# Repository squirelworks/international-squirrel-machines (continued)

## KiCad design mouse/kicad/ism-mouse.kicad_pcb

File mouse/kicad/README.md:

# ISM Mouse — KiCad

Generated by `python3 scripts/build_mouse.py`.

| File | Role |
|------|------|
| `ism-mouse.kicad_sch` / `.kicad_pcb` / `.kicad_pro` | Project |
| `sym-lib-table` / `fp-lib-table` | Project-local tables (`${KIPRJMOD}/../../common/kicad`, `${KICAD8_*}`) |
| `erc.rpt` / `drc.rpt` | Last `--severity-error` reports (expect 0 errors) |

Shared symbols / optical-sensor footprint: `common/kicad/`.

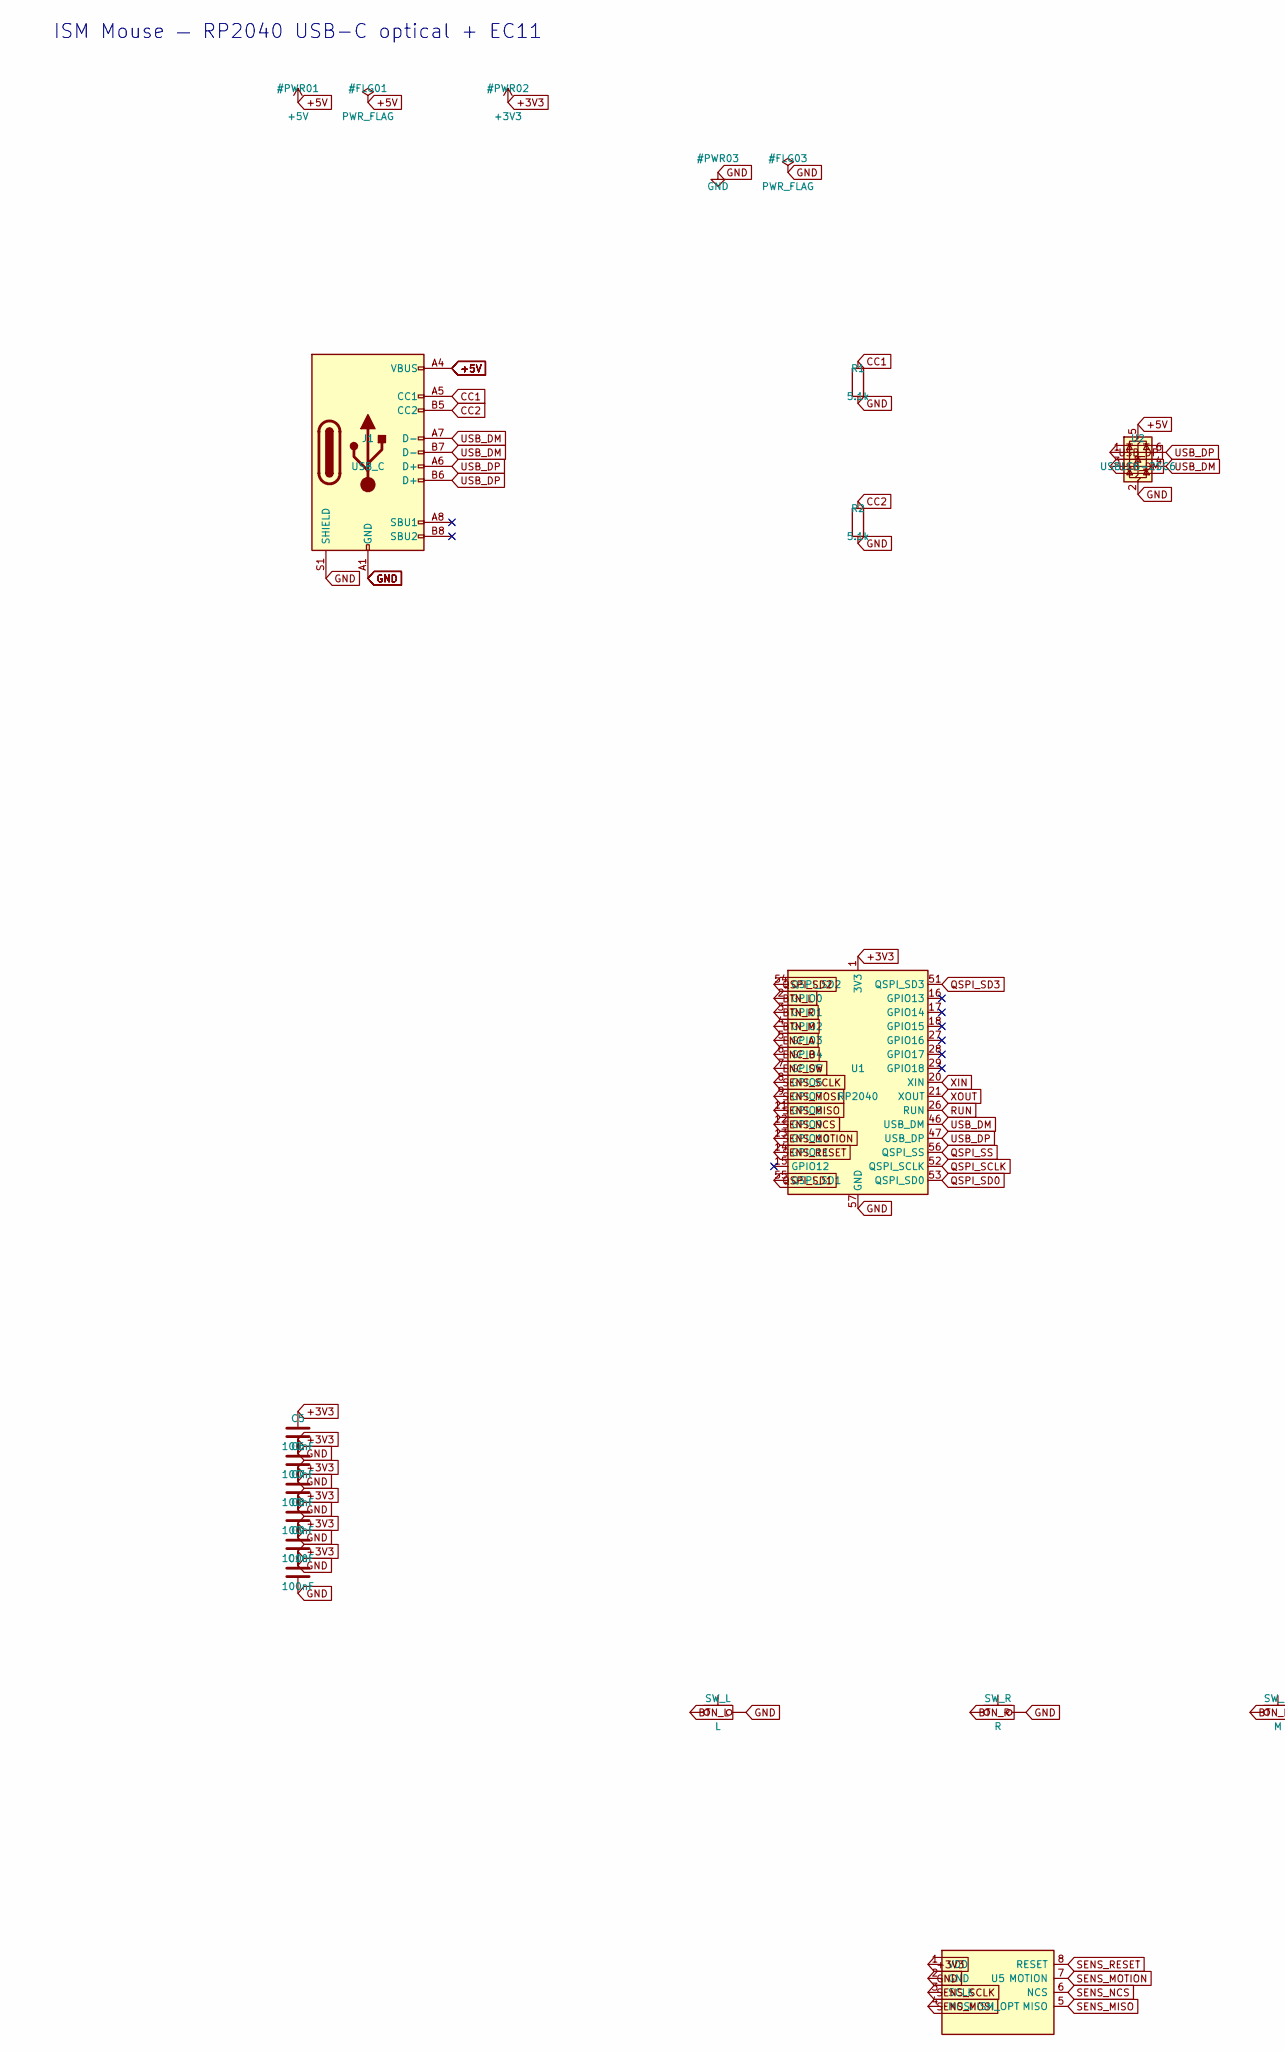
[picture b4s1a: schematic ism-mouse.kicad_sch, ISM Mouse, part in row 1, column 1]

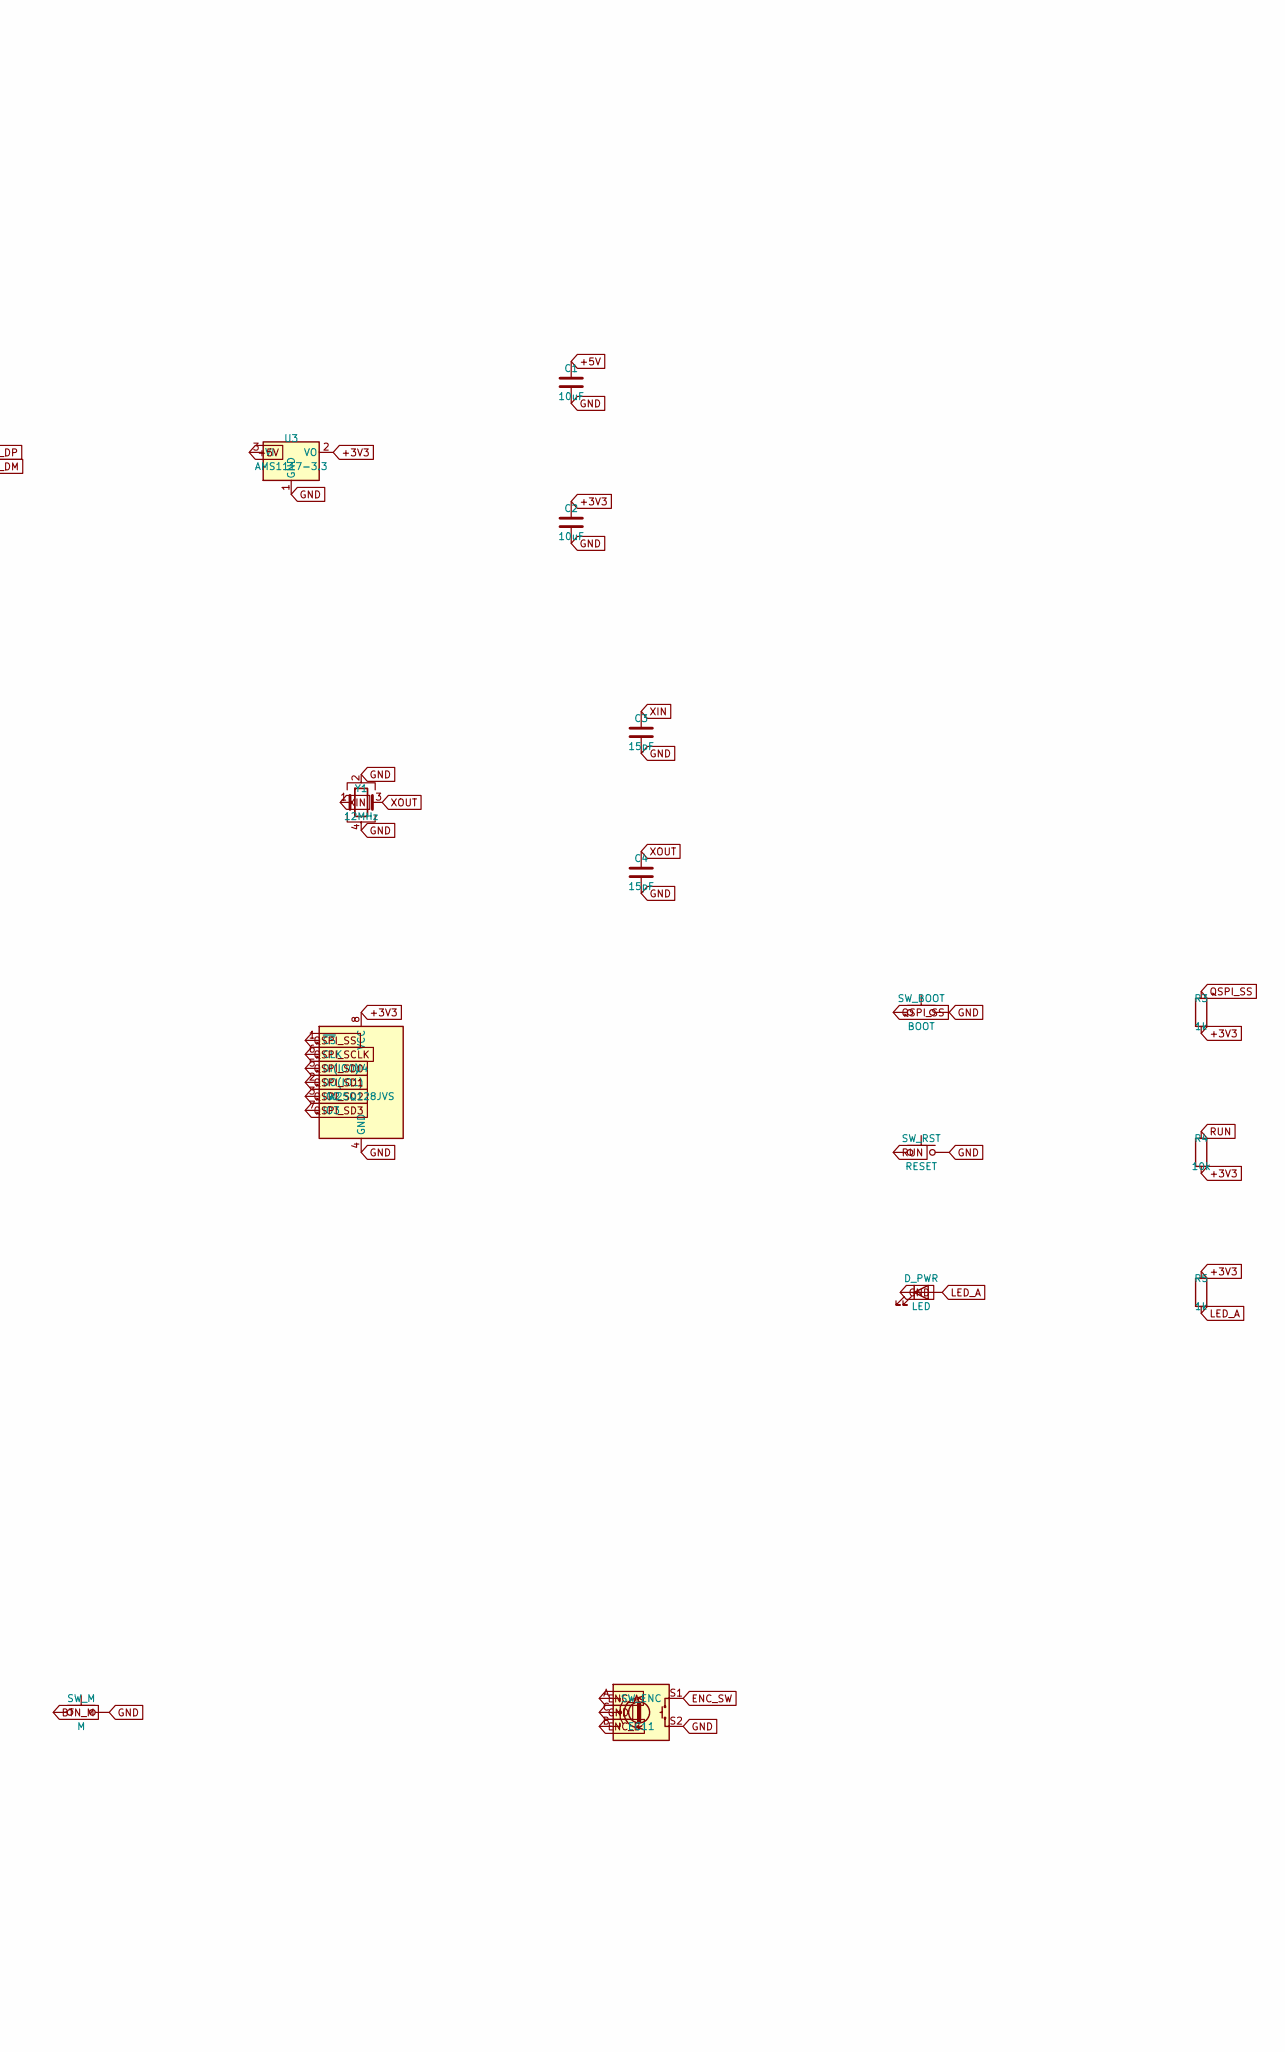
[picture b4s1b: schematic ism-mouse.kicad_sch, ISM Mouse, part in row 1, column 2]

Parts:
C1, C2: 10uF; C_0805_2012Metric; LCSC C15850
C3, C4: 15pF; C_0603_1608Metric; LCSC C1007
C5, C6, C7, C8, C9, C10: 100nF; C_0603_1608Metric; LCSC C14663
D_PWR: LED; LED_0603_1608Metric; LCSC C2286
J1: USB_C; USB_C_Receptacle_GCT_USB4105-xx-A_16P_TopMnt_Horizontal; MPN USB4105-GF-A; LCSC C165948
R1, R2: 5.1k; R_0603_1608Metric; LCSC C23244
R3, R5: 1k; R_0603_1608Metric; LCSC C21190
R4: 10k; R_0603_1608Metric; LCSC C25804
SW_BOOT: BOOT; SW_SPST_PTS645; LCSC C318884
SW_ENC: EC11; RotaryEncoder_Alps_EC11E-Switch_Vertical_H20mm; MPN EC11E; LCSC C318975
SW_L: L; SW_SPST_PTS645; LCSC C318884
SW_M: M; SW_SPST_PTS645; LCSC C318884
SW_R: R; SW_SPST_PTS645; LCSC C318884
SW_RST: RESET; SW_SPST_PTS645; LCSC C318884
U1: RP2040; QFN-56-1EP_7x7mm_P0.4mm_EP3.2x3.2mm; MPN RP2040; LCSC C2040
U2: USBLC6-2SC6; SOT-23-6; LCSC C7519
U3: AMS1117-3.3; TO-252-3_TabPin2; LCSC C6187
U4: W25Q128JVS; SOIC-8_3.9x4.9mm_P1.27mm; LCSC C97521
U5: ISM_OPT; ISM_OpticalSensor_8pad; MPN ISM-OPT-1
Y1: 12MHz; Crystal_SMD_3225-4Pin_3.2x2.5mm; LCSC C13713

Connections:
+3V3: C2.1, C5.1, C6.1, C7.1, C8.1, C9.1, C10.1, R3.2, R4.2, R5.1, U1.1 (3V3), U1.10, U1.22, U1.23, U1.33, U1.42, U1.43, U1.44, U1.45, U1.48, U1.49, U1.50, U3.2 (VO), U4.8 (VCC), U5.1 (VDD)
+5V: C1.1, J1.A4 (VBUS), J1.A9 (VBUS), J1.B4 (VBUS), J1.B9 (VBUS), U2.5 (VBUS), U3.3 (VI)
BTN_L: SW_L.1, U1.2 (GPIO0)
BTN_M: SW_M.1, U1.4 (GPIO2)
BTN_R: SW_R.1, U1.3 (GPIO1)
CC1: J1.A5 (CC1), R1.1
CC2: J1.B5 (CC2), R2.1
ENC_A: SW_ENC.A, U1.5 (GPIO3)
ENC_B: SW_ENC.B, U1.6 (GPIO4)
ENC_SW: SW_ENC.S1, U1.7 (GPIO5)
GND: C1.2, C2.2, C3.2, C4.2, C5.2, C6.2, C7.2, C8.2, C9.2, C10.2, D_PWR.1 (K), J1.A1 (GND), J1.A8 (SBU1), J1.A12 (GND), J1.B1 (GND), J1.B8 (SBU2), J1.B12 (GND), J1.S1 (SHIELD), R1.2, R2.2, SW_BOOT.2, SW_ENC.C, SW_ENC.S2, SW_L.2, SW_M.2, SW_R.2, SW_RST.2, U1.19, U1.57 (GND), U2.2 (GND), U3.1 (GND), U4.4 (GND), U5.2 (GND), Y1.2, Y1.4; also elsewhere on the board
LED_A: D_PWR.2 (A), R5.2
QSPI_SCLK: U1.52 (QSPI_SCLK), U4.6 (CLK)
QSPI_SD0: U1.53 (QSPI_SD0), U4.5 (DI(IO0))
QSPI_SD1: U1.55 (QSPI_SD1), U4.2 (DO(IO1))
QSPI_SD2: U1.54 (QSPI_SD2), U4.3 (IO2)
QSPI_SD3: U1.51 (QSPI_SD3), U4.7 (IO3)
QSPI_SS: R3.1, SW_BOOT.1, U1.56 (QSPI_SS), U4.1 (~CS)
RUN: R4.1, SW_RST.1, U1.26 (RUN)
SENS_MISO: U1.11 (GPIO8), U5.5 (MISO)
SENS_MOSI: U1.9 (GPIO7), U5.4 (MOSI)
SENS_MOTION: U1.13 (GPIO10), U5.7 (MOTION)
SENS_NCS: U1.12 (GPIO9), U5.6 (NCS)
SENS_RESET: U1.14 (GPIO11), U5.8 (RESET)
SENS_SCLK: U1.8 (GPIO6), U5.3 (SCLK)
USB_DM: J1.A7 (D-), J1.B7 (D-), U1.46 (USB_DM), U2.3 (I/O2), U2.4 (I/O2)
USB_DP: J1.A6 (D+), J1.B6 (D+), U1.47 (USB_DP), U2.1 (I/O1), U2.6 (I/O1)
XIN: C3.1, U1.20 (XIN), Y1.1
XOUT: C4.1, U1.21 (XOUT), Y1.3

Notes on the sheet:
ISM Mouse — RP2040 USB-C optical + EC11

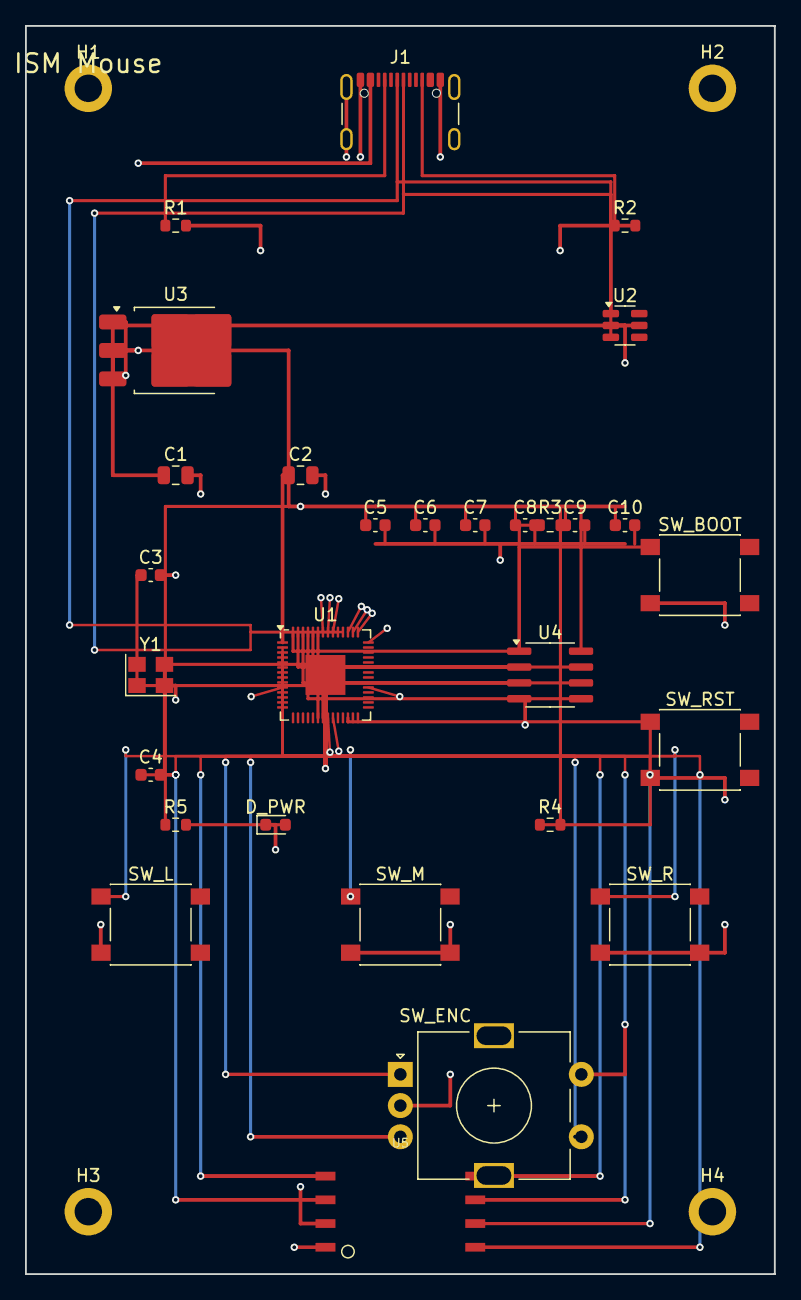
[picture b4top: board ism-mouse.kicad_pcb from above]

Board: 4 copper layers, 60.0 x 100.0 mm, 33 parts (0 on the bottom side), 29 nets.

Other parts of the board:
H1, H2, H3, H4: M2; MountingHole_2.2mm_M2_DIN965_Pad

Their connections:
GND: H1.1, H2.1, H3.1, H4.1; also elsewhere on the board

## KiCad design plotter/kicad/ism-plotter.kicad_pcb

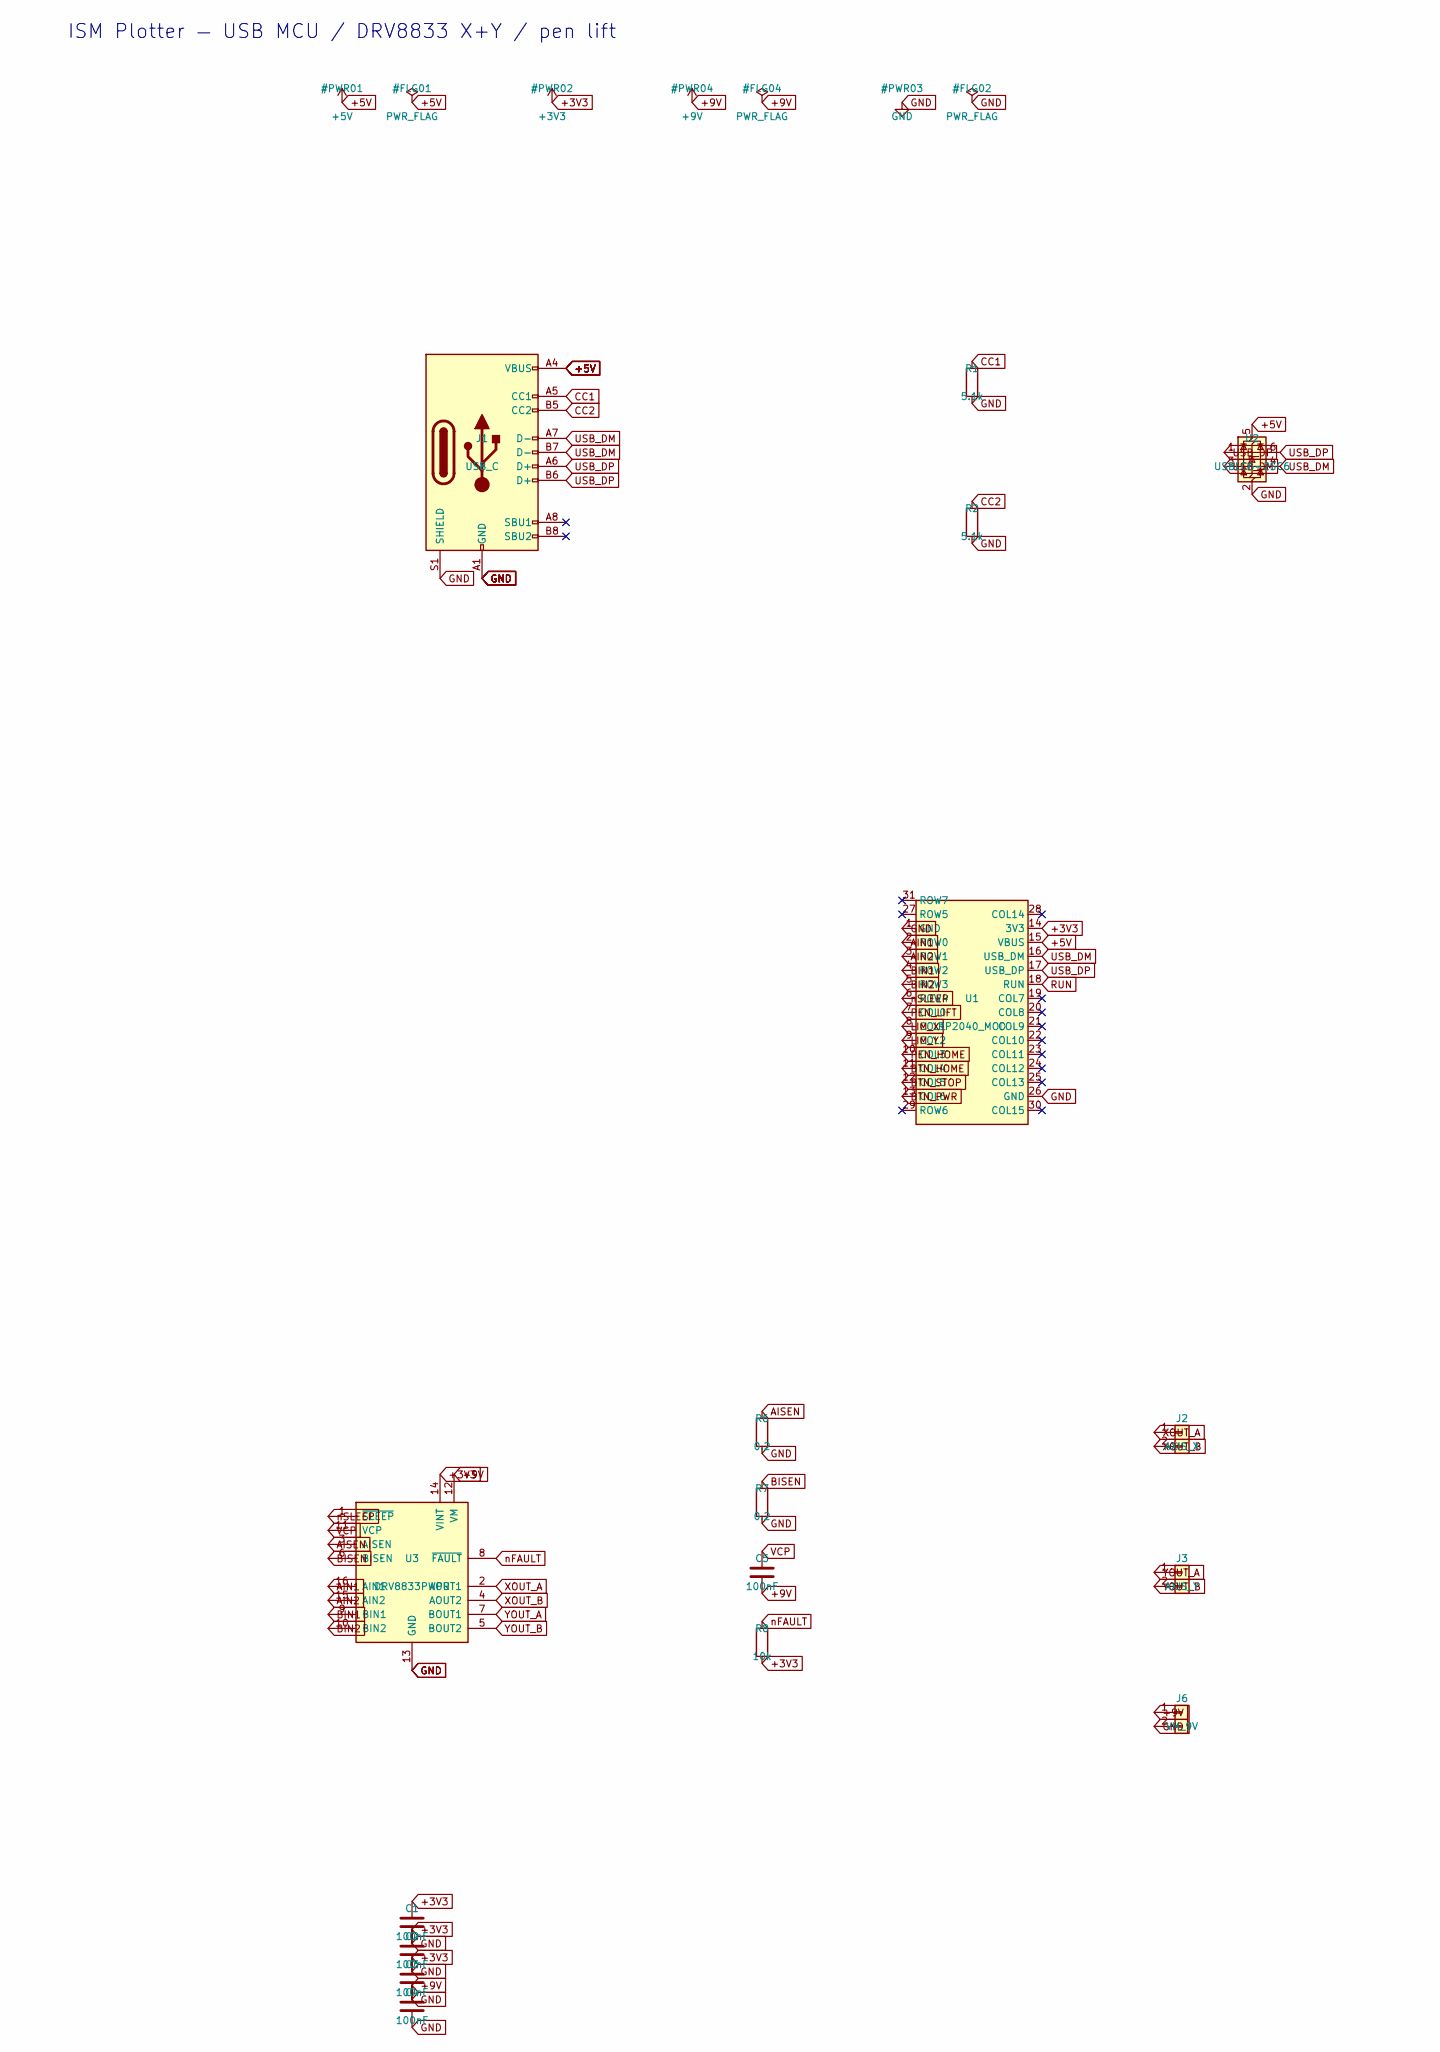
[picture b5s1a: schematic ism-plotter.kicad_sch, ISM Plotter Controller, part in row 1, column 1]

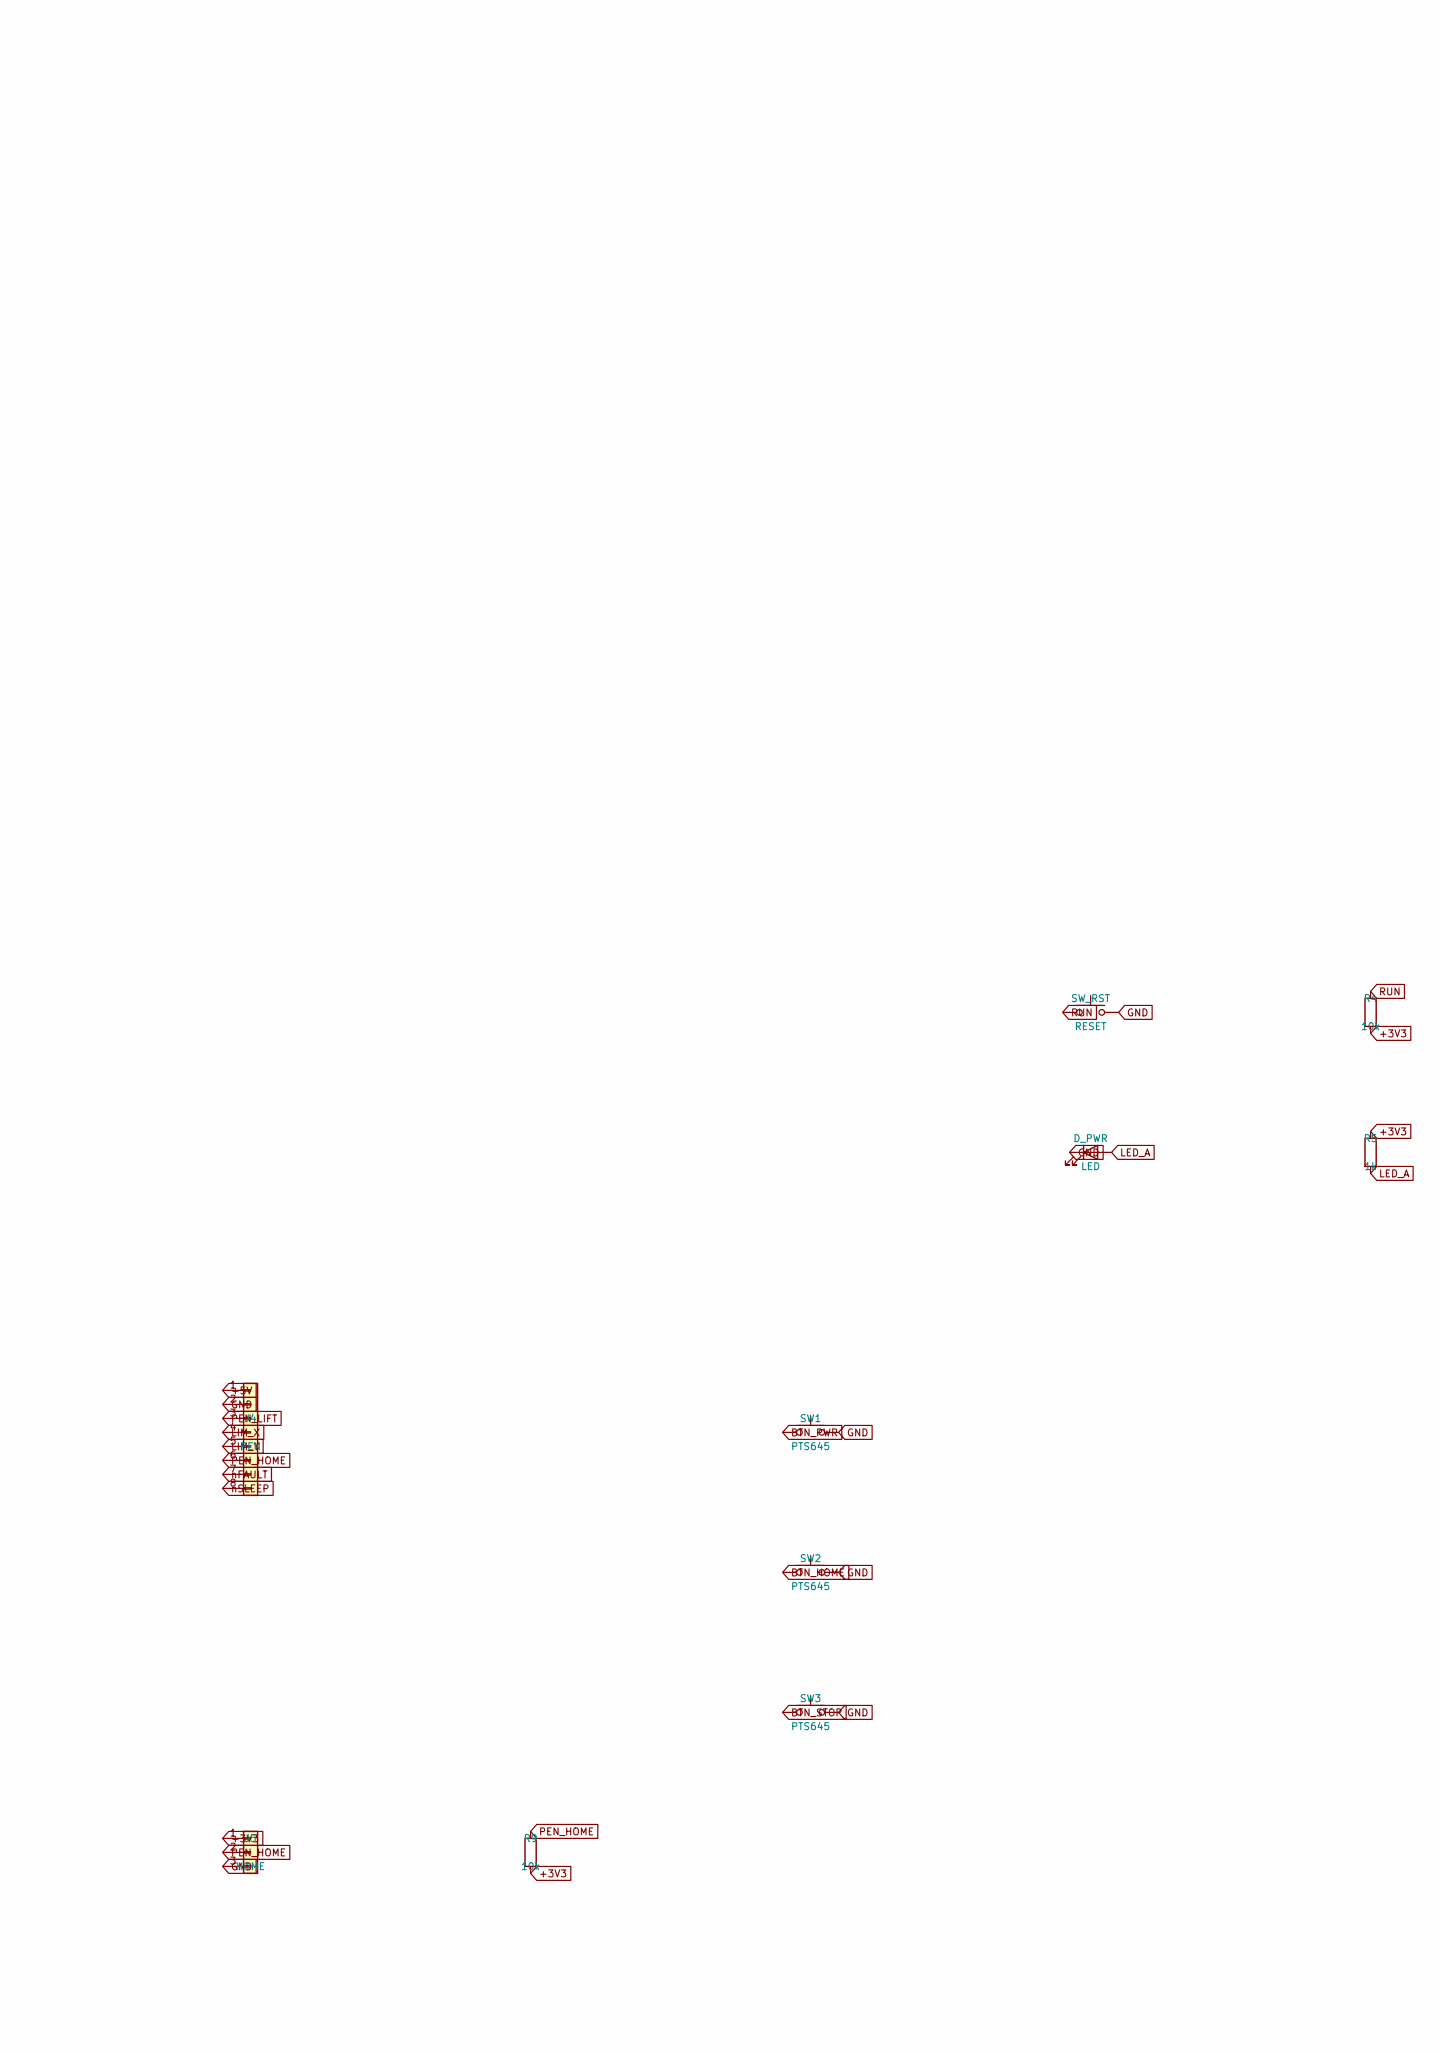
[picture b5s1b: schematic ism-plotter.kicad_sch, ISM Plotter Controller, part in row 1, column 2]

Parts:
C1, C2, C3, C4, C5: 100nF; C_0603_1608Metric; LCSC C14663
D_PWR: LED; LED_0603_1608Metric; LCSC C2286
J1: USB_C; USB_C_Receptacle_GCT_USB4105-xx-A_16P_TopMnt_Horizontal; LCSC C165948
J2: AXIS_X; PinHeader_1x02_P2.54mm_Vertical
J3: AXIS_Y; PinHeader_1x02_P2.54mm_Vertical
J4: PEN; PinHeader_1x08_P2.54mm_Vertical
J5: HOME; PinHeader_1x03_P2.54mm_Vertical
J6: VM_9V; PinHeader_1x02_P2.54mm_Vertical
R1, R2: 5.1k; R_0603_1608Metric; LCSC C23244
R4, R8, R9: 10k; R_0603_1608Metric; LCSC C25804
R5: 1k; R_0603_1608Metric; LCSC C21190
R6, R7: 0.2; R_0603_1608Metric; LCSC C17410
SW1, SW2, SW3: PTS645; SW_SPST_PTS645; LCSC C318884
SW_RST: RESET; SW_SPST_PTS645; LCSC C318884
U1: RP2040_MOD; ISM_RP2040_Module; MPN ISM-RP2040-MOD
U2: USBLC6-2SC6; SOT-666; LCSC C7519
U3: DRV8833PWPR; HTSSOP-16-1EP_4.4x5mm_P0.65mm_EP3.4x5mm_Mask2.46x2.31mm; MPN DRV8833PWPR; LCSC C50506

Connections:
+3V3: C1.1, C2.1, C3.1, J5.1, R4.2, R5.1, R8.2, R9.2, U1.14 (3V3), U3.14 (VINT)
+5V: J1.A4 (VBUS), J1.A9 (VBUS), J1.B4 (VBUS), J1.B9 (VBUS), J4.1, U1.15 (VBUS), U2.5 (VBUS)
+9V: C4.1, C5.2, J6.1, U3.12 (VM)
AIN1: U1.2 (ROW0), U3.16 (AIN1)
AIN2: U1.3 (ROW1), U3.15 (AIN2)
AISEN: R6.1, U3.3 (AISEN)
BIN1: U1.4 (ROW2), U3.9 (BIN1)
BIN2: U1.5 (ROW3), U3.10 (BIN2)
BISEN: R7.1, U3.6 (BISEN)
BTN_HOME: SW2.1, U1.11 (COL4)
BTN_PWR: SW1.1, U1.13 (COL6)
BTN_STOP: SW3.1, U1.12 (COL5)
CC1: J1.A5 (CC1), R1.1
CC2: J1.B5 (CC2), R2.1
GND: C1.2, C2.2, C3.2, C4.2, D_PWR.1 (K), J1.A1 (GND), J1.A8 (SBU1), J1.A12 (GND), J1.B1 (GND), J1.B8 (SBU2), J1.B12 (GND), J1.S1 (SHIELD), J4.2, J5.3, J6.2, R1.2, R2.2, R6.2, R7.2, SW1.2, SW2.2, SW3.2, SW_RST.2, U1.1 (GND), U1.26 (GND), U2.2 (GND), U3.13 (GND), U3.17 (GND)
LED_A: D_PWR.2 (A), R5.2
LIM_X: J4.4, U1.8 (COL1)
LIM_Y: J4.5, U1.9 (COL2)
PEN_HOME: J4.6, J5.2, R9.1, U1.10 (COL3)
PEN_LIFT: J4.3, U1.7 (COL0)
RUN: R4.1, SW_RST.1, U1.18 (RUN)
USB_DM: J1.A7 (D-), J1.B7 (D-), U1.16 (USB_DM), U2.3 (I/O2), U2.4 (I/O2)
USB_DP: J1.A6 (D+), J1.B6 (D+), U1.17 (USB_DP), U2.1 (I/O1), U2.6 (I/O1)
VCP: C5.1, U3.11 (VCP)
XOUT_A: J2.1, U3.2 (AOUT1)
XOUT_B: J2.2, U3.4 (AOUT2)
YOUT_A: J3.1, U3.7 (BOUT1)
YOUT_B: J3.2, U3.5 (BOUT2)
nFAULT: J4.7, R8.1, U3.8 (~FAULT)
nSLEEP: J4.8, U1.6 (ROW4), U3.1 (~SLEEP)

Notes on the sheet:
ISM Plotter — USB MCU / DRV8833 X+Y / pen lift

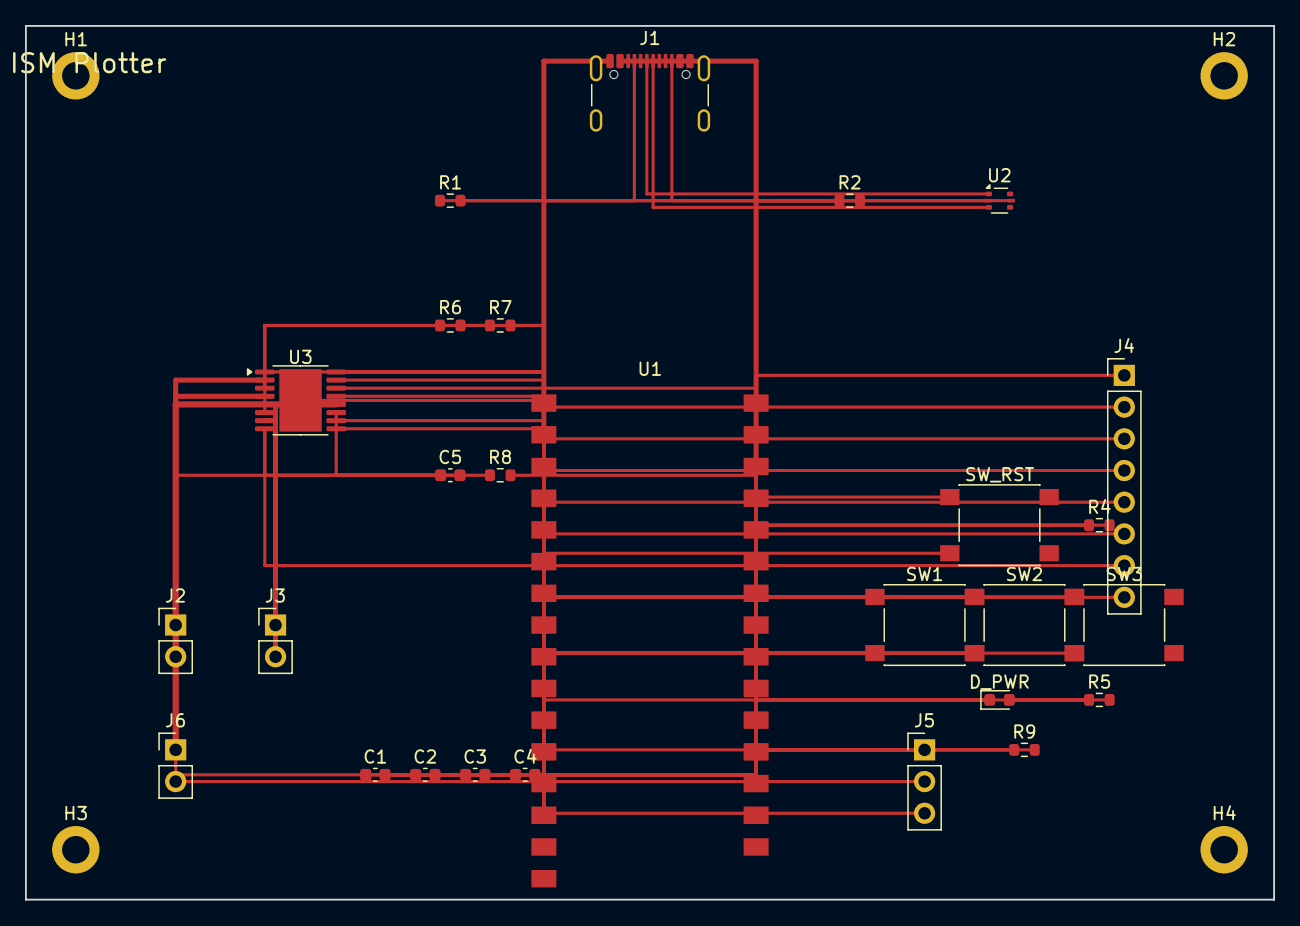
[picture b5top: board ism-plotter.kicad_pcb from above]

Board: 4 copper layers, 100.0 x 70.0 mm, 31 parts (0 on the bottom side), 30 nets.

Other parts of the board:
H1, H2, H3, H4: M2; MountingHole_2.2mm_M2_DIN965_Pad

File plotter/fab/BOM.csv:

Designator,Value,Footprint,Quantity,Manufacturer,MPN,LCSC,Notes
U1,RP2040_MOD,ISM_RP2040_Module,1,ISM,ISM-RP2040-MOD,,No LCSC — custom ISM carrier
U2,USBLC6-2SC6,SOT-666,1,ST,USBLC6-2SC6,C7519,ESD
U3,DRV8833PWPR,HTSSOP-16-EP,1,TI,DRV8833PWPR,C50506,Default dual H-bridge — X + Y axes
J1,USB4105,GCT USB-C 16P,1,GCT,USB4105-GF-A,C165948,
"J2,J3,J6",1x02,PinHeader 1x02,3,,HDR-1x2,C124376,Axes / VM
J4,PEN,PinHeader 1x08,1,,HDR-1x8,C124405,Pen interface
J5,HOME,PinHeader 1x03,1,,HDR-1x3,C124401,Home / limits
"R1,R2",5.1k,0603,2,,5.1k,C23244,CC
"R4,R8,R9",10k,0603,3,,10k,C25804,
R5,1k,0603,1,,1k,C21190,
"R6,R7",0.2,0603,2,,0.2R,C17410,Sense
C1-C5,100nF,0603,5,,100nF,C14663,
D_PWR,LED,0603,1,,LED,C2286,
"SW1-SW3,SW_RST",PTS645,PTS645,4,,PTS645,C318884,
H1-H4,M2,MountingHole,4,,,,No LCSC — mechanical NPTH
